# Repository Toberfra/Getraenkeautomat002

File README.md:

# Getraenkeautomat002
Ein Cocktailmixer:

Er Besteht aus mehreren Komponenten:
  - Vielen Peristalik Pumpen.
    - Diese können 3D gedruckt werden. Siehe Hardware/Pumpe/Pumpe3
    - Sie werden von einem Nema 17 Schrittmotor angetrieben.
  - Motor ansteuerung der Schrittmotoren.
    - Sotware für ATmege32
  - Datenbank (MariaDB)
    - Rezepte der Getränke
    - Daten der einzelnen Punmpen
    - Daten der Gläser
  - Sofware zum Bestellen und Ansteuerung der Pumpen

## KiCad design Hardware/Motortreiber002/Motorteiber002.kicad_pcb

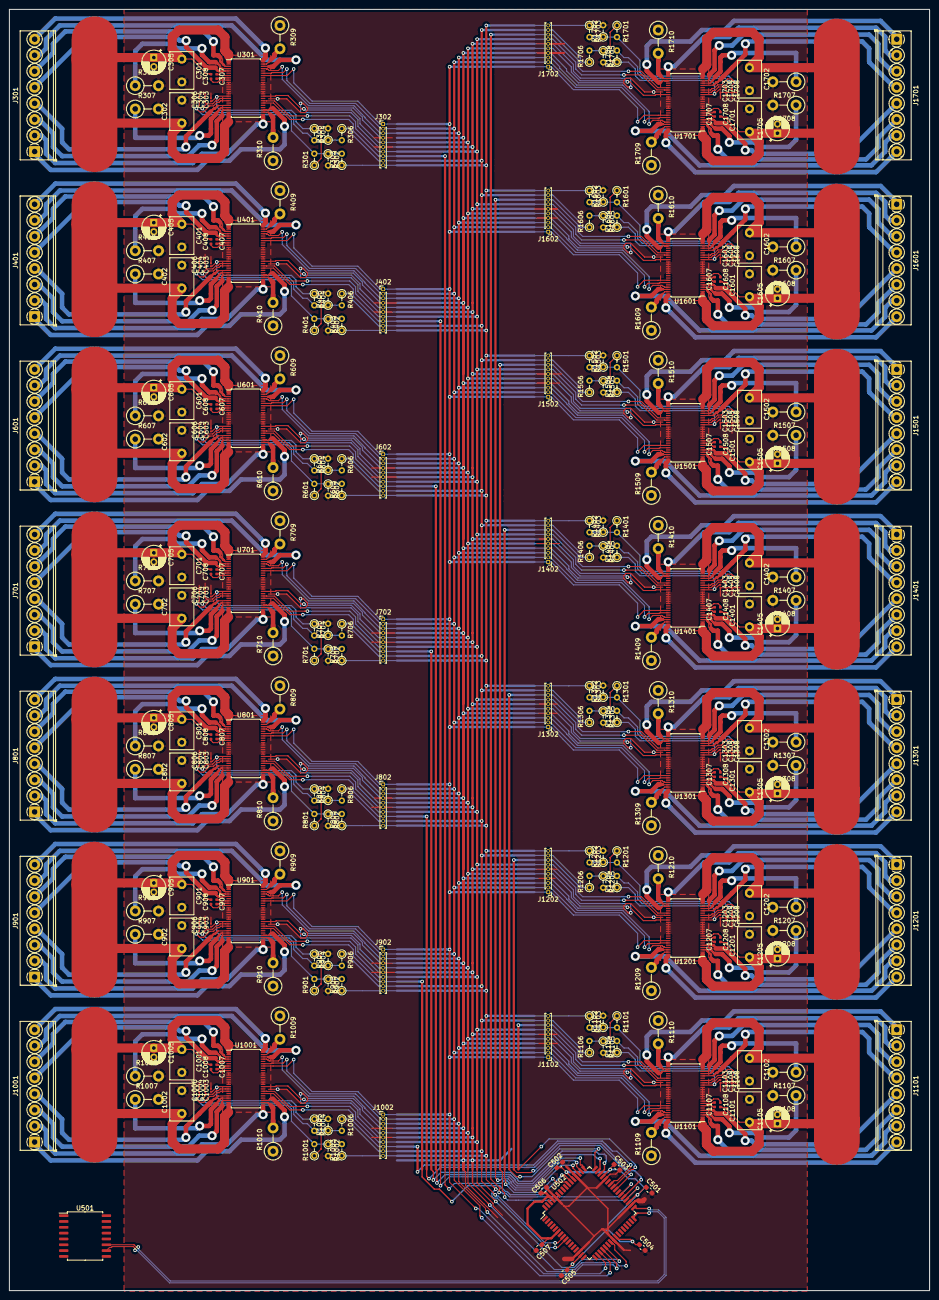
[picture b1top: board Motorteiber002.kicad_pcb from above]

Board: 2 copper layers, 200.7 x 279.4 mm, 303 parts (0 on the bottom side), 292 nets.

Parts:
C301, C302, C401, C402, C601, C602, C701, C702, C801, C802, C901, C902, C1001, C1002, C1101, C1102, C1201, C1202, C1301, C1302, C1401, C1402, C1501, C1502, C1601, C1602, C1701, C1702: 100nF; C_Disc_D8.0mm_W5.0mm_P5.00mm
C303, C403, C603, C703, C803, C903, C1003, C1103, C1203, C1303, C1403, C1503, C1603, C1703: 100nF 6,3V; C_0201_0603Metric
C304, C306, C404, C406, C604, C606, C704, C706, C804, C806, C904, C906, C1004, C1006, C1104, C1106, C1204, C1206, C1304, C1306, C1404, C1406, C1504, C1506, C1604, C1606, C1704, C1706: 1nF 25V; C_0201_0603Metric
C305, C405, C605, C705, C805, C905, C1005, C1105, C1205, C1305, C1405, C1505, C1605, C1705: 33uF 35V; CP_Radial_D5.0mm_P2.00mm
C307, C407, C607, C707, C807, C907, C1007, C1107, C1207, C1307, C1407, C1507, C1607, C1707: 10nF 50V; C_0402_1005Metric
C308, C408, C608, C708, C808, C908, C1008, C1108, C1208, C1308, C1408, C1508, C1608, C1708: 100nF 16V; C_0402_1005Metric
C501, C502, C503, C504, C505, C506, C507: 100nF; C_0603_1608Metric_Pad1.05x0.95mm_HandSolder
J301, J401, J601, J701, J801, J901, J1001, J1101, J1201, J1301, J1401, J1501, J1601, J1701: Screw_Terminal_01x08; TerminalBlock_Phoenix_PT-1,5-8-3.5-H_1x08_P3.50mm_Horizontal
J302, J402, J602, J702, J802, J902, J1002, J1102, J1202, J1302, J1402, J1502, J1602, J1702: Conn_01x10_Male; PinHeader_1x10_P1.00mm_Vertical
R301, R302, R304, R305, R401, R402, R404, R405, R601, R602, R604, R605, R701, R702, R704, R705, R801, R802, R804, R805, R901, R902, R904, R905, R1001, R1002, R1004, R1005, R1101, R1102, R1104, R1105, R1201, R1202, R1204, R1205, R1301, R1302, R1304, R1305, R1401, R1402, R1404, R1405, R1501, R1502, R1504, R1505, R1601, R1602, R1604, R1605, R1701, R1702, R1704, R1705: R; R_Axial_DIN0204_L3.6mm_D1.6mm_P2.54mm_Vertical
R303, R306, R403, R406, R603, R606, R703, R706, R803, R806, R903, R906, R1003, R1006, R1103, R1106, R1203, R1206, R1303, R1306, R1403, R1406, R1503, R1506, R1603, R1606, R1703, R1706: 1; R_Axial_DIN0204_L3.6mm_D1.6mm_P2.54mm_Vertical
R307, R308, R309, R310, R407, R408, R409, R410, R607, R608, R609, R610, R707, R708, R709, R710, R807, R808, R809, R810, R907, R908, R909, R910, R1007, R1008, R1009, R1010, R1107, R1108, R1109, R1110, R1207, R1208, R1209, R1210, R1307, R1308, R1309, R1310, R1407, R1408, R1409, R1410, R1507, R1508, R1509, R1510, R1607, R1608, R1609, R1610, R1707, R1708, R1709, R1710: 0R5; R_Axial_DIN0411_L9.9mm_D3.6mm_P5.08mm_Vertical
U301, U401, U601, U701, U801, U901, U1001, U1101, U1201, U1301, U1401, U1501, U1601, U1701: DRV8823; TSSOP-48_6.1x12.5mm_P0.5mm
U501: ADUM3160; SOIC-16W_7.5x10.3mm_P1.27mm
U502: ATxmega128C3-AU; TQFP-64_14x14mm_P0.8mm

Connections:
+5V: C501.1, C502.1, C503.1, C504.1, C505.1, U502.15, U502.25, U502.35, U502.45, U502.53
+5VA: C506.1, C507.1, U502.6, U502.61
/Controller/D+: U501.10, U502.33
/Controller/D-: U501.11, U502.32
/Motortreiber0/MA1: J701.5, U701.5
/Motortreiber0/MA2: J701.6, U701.3
/Motortreiber0/MAR: R708.1, U701.4
/Motortreiber0/MB1: J701.7, U701.46
/Motortreiber0/MB2: J701.8, U701.48
/Motortreiber0/MBR: R709.2, U701.47
/Motortreiber0/MC1: J701.1, U701.27
/Motortreiber0/MC2: J701.2, U701.25
/Motortreiber0/MCR: R710.2, U701.26
/Motortreiber0/MD1: J701.3, U701.22
/Motortreiber0/MD2: J701.4, U701.20
/Motortreiber0/MDR: R707.1, U701.21
/Motortreiber1/MA1: J601.5, U601.5
/Motortreiber1/MA2: J601.6, U601.3
/Motortreiber1/MAR: R608.1, U601.4
/Motortreiber1/MB1: J601.7, U601.46
/Motortreiber1/MB2: J601.8, U601.48
/Motortreiber1/MBR: R609.2, U601.47
/Motortreiber1/MC1: J601.1, U601.27
/Motortreiber1/MC2: J601.2, U601.25
/Motortreiber1/MCR: R610.2, U601.26
/Motortreiber1/MD1: J601.3, U601.22
/Motortreiber1/MD2: J601.4, U601.20
/Motortreiber1/MDR: R607.1, U601.21
/Motortreiber2/MA1: J1301.5, U1301.5
/Motortreiber2/MA2: J1301.6, U1301.3
/Motortreiber2/MAR: R1308.1, U1301.4
/Motortreiber2/MB1: J1301.7, U1301.46
/Motortreiber2/MB2: J1301.8, U1301.48
/Motortreiber2/MBR: R1309.2, U1301.47
/Motortreiber2/MC1: J1301.1, U1301.27
/Motortreiber2/MC2: J1301.2, U1301.25
/Motortreiber2/MCR: R1310.2, U1301.26
/Motortreiber2/MD1: J1301.3, U1301.22
/Motortreiber2/MD2: J1301.4, U1301.20
/Motortreiber2/MDR: R1307.1, U1301.21
/Motortreiber3/MA1: J401.5, U401.5
/Motortreiber3/MA2: J401.6, U401.3
/Motortreiber3/MAR: R408.1, U401.4
/Motortreiber3/MB1: J401.7, U401.46
/Motortreiber3/MB2: J401.8, U401.48
/Motortreiber3/MBR: R409.2, U401.47
/Motortreiber3/MC1: J401.1, U401.27
/Motortreiber3/MC2: J401.2, U401.25
/Motortreiber3/MCR: R410.2, U401.26
/Motortreiber3/MD1: J401.3, U401.22
/Motortreiber3/MD2: J401.4, U401.20
/Motortreiber3/MDR: R407.1, U401.21
/Motortreiber4/MA1: J1601.5, U1601.5
/Motortreiber4/MA2: J1601.6, U1601.3
/Motortreiber4/MAR: R1608.1, U1601.4
/Motortreiber4/MB1: J1601.7, U1601.46
/Motortreiber4/MB2: J1601.8, U1601.48
/Motortreiber4/MBR: R1609.2, U1601.47
/Motortreiber4/MC1: J1601.1, U1601.27
/Motortreiber4/MC2: J1601.2, U1601.25
/Motortreiber4/MCR: R1610.2, U1601.26
/Motortreiber4/MD1: J1601.3, U1601.22
/Motortreiber4/MD2: J1601.4, U1601.20
/Motortreiber4/MDR: R1607.1, U1601.21
/Motortreiber5/MA1: J301.5, U301.5
/Motortreiber5/MA2: J301.6, U301.3
/Motortreiber5/MAR: R308.1, U301.4
/Motortreiber5/MB1: J301.7, U301.46
/Motortreiber5/MB2: J301.8, U301.48
/Motortreiber5/MBR: R309.2, U301.47
/Motortreiber5/MC1: J301.1, U301.27
/Motortreiber5/MC2: J301.2, U301.25
/Motortreiber5/MCR: R310.2, U301.26
/Motortreiber5/MD1: J301.3, U301.22
/Motortreiber5/MD2: J301.4, U301.20
/Motortreiber5/MDR: R307.1, U301.21
/Motortreiber6/MA1: J901.5, U901.5
/Motortreiber6/MA2: J901.6, U901.3
/Motortreiber6/MAR: R908.1, U901.4
/Motortreiber6/MB1: J901.7, U901.46
/Motortreiber6/MB2: J901.8, U901.48
/Motortreiber6/MBR: R909.2, U901.47
/Motortreiber6/MC1: J901.1, U901.27
/Motortreiber6/MC2: J901.2, U901.25
/Motortreiber6/MCR: R910.2, U901.26
/Motortreiber6/MD1: J901.3, U901.22
/Motortreiber6/MD2: J901.4, U901.20
/Motortreiber6/MDR: R907.1, U901.21
/Motortreiber7/MA1: J1401.5, U1401.5
/Motortreiber7/MA2: J1401.6, U1401.3
/Motortreiber7/MAR: R1408.1, U1401.4
/Motortreiber7/MB1: J1401.7, U1401.46
/Motortreiber7/MB2: J1401.8, U1401.48
/Motortreiber7/MBR: R1409.2, U1401.47
/Motortreiber7/MC1: J1401.1, U1401.27
/Motortreiber7/MC2: J1401.2, U1401.25
/Motortreiber7/MCR: R1410.2, U1401.26
/Motortreiber7/MD1: J1401.3, U1401.22
/Motortreiber7/MD2: J1401.4, U1401.20
/Motortreiber7/MDR: R1407.1, U1401.21
/Motortreiber8/MA1: J1501.5, U1501.5
/Motortreiber8/MA2: J1501.6, U1501.3
/Motortreiber8/MAR: R1508.1, U1501.4
/Motortreiber8/MB1: J1501.7, U1501.46
/Motortreiber8/MB2: J1501.8, U1501.48
/Motortreiber8/MBR: R1509.2, U1501.47
/Motortreiber8/MC1: J1501.1, U1501.27
/Motortreiber8/MC2: J1501.2, U1501.25
/Motortreiber8/MCR: R1510.2, U1501.26
/Motortreiber8/MD1: J1501.3, U1501.22
/Motortreiber8/MD2: J1501.4, U1501.20
/Motortreiber8/MDR: R1507.1, U1501.21
/Motortreiber9/MA1: J801.5, U801.5
/Motortreiber9/MA2: J801.6, U801.3
/Motortreiber9/MAR: R808.1, U801.4
/Motortreiber9/MB1: J801.7, U801.46
/Motortreiber9/MB2: J801.8, U801.48
/Motortreiber9/MBR: R809.2, U801.47
/Motortreiber9/MC1: J801.1, U801.27
/Motortreiber9/MC2: J801.2, U801.25
/Motortreiber9/MCR: R810.2, U801.26
/Motortreiber9/MD1: J801.3, U801.22
/Motortreiber9/MD2: J801.4, U801.20
/Motortreiber9/MDR: R807.1, U801.21
/Motortreiber10/MA1: J1701.5, U1701.5
/Motortreiber10/MA2: J1701.6, U1701.3
/Motortreiber10/MAR: R1708.1, U1701.4
/Motortreiber10/MB1: J1701.7, U1701.46
/Motortreiber10/MB2: J1701.8, U1701.48
/Motortreiber10/MBR: R1709.2, U1701.47
/Motortreiber10/MC1: J1701.1, U1701.27
/Motortreiber10/MC2: J1701.2, U1701.25
/Motortreiber10/MCR: R1710.2, U1701.26
/Motortreiber10/MD1: J1701.3, U1701.22
/Motortreiber10/MD2: J1701.4, U1701.20
/Motortreiber10/MDR: R1707.1, U1701.21
/Motortreiber12/MA1: J1201.5, U1201.5
/Motortreiber12/MA2: J1201.6, U1201.3
/Motortreiber12/MAR: R1208.1, U1201.4
/Motortreiber12/MB1: J1201.7, U1201.46
/Motortreiber12/MB2: J1201.8, U1201.48
/Motortreiber12/MBR: R1209.2, U1201.47
/Motortreiber12/MC1: J1201.1, U1201.27
/Motortreiber12/MC2: J1201.2, U1201.25
/Motortreiber12/MCR: R1210.2, U1201.26
/Motortreiber12/MD1: J1201.3, U1201.22
/Motortreiber12/MD2: J1201.4, U1201.20
/Motortreiber12/MDR: R1207.1, U1201.21
/Motortreiber13/MA1: J1101.5, U1101.5
/Motortreiber13/MA2: J1101.6, U1101.3
/Motortreiber13/MAR: R1108.1, U1101.4
/Motortreiber13/MB1: J1101.7, U1101.46
/Motortreiber13/MB2: J1101.8, U1101.48
/Motortreiber13/MBR: R1109.2, U1101.47
/Motortreiber13/MC1: J1101.1, U1101.27
/Motortreiber13/MC2: J1101.2, U1101.25
/Motortreiber13/MCR: R1110.2, U1101.26
/Motortreiber13/MD1: J1101.3, U1101.22
/Motortreiber13/MD2: J1101.4, U1101.20
/Motortreiber13/MDR: R1107.1, U1101.21
/Motortreiber14/MA1: J1001.5, U1001.5
/Motortreiber14/MA2: J1001.6, U1001.3
/Motortreiber14/MAR: R1008.1, U1001.4
/Motortreiber14/MB1: J1001.7, U1001.46
/Motortreiber14/MB2: J1001.8, U1001.48
/Motortreiber14/MBR: R1009.2, U1001.47
/Motortreiber14/MC1: J1001.1, U1001.27
/Motortreiber14/MC2: J1001.2, U1001.25
/Motortreiber14/MCR: R1010.2, U1001.26
/Motortreiber14/MD1: J1001.3, U1001.22
/Motortreiber14/MD2: J1001.4, U1001.20
/Motortreiber14/MDR: R1007.1, U1001.21
/Steuer0: J302.2, J402.2, J602.2, J702.2, J802.2, J902.2, J1002.2, J1102.2, J1202.2, J1302.2, J1402.2, J1502.2, J1602.2, J1702.2, U301.43, U401.43, U502.19, U601.43, U701.43, U801.43, U901.43, U1001.43, U1101.43, U1201.43, U1301.43, U1401.43, U1501.43, U1601.43, U1701.43
/Steuer1: J302.1, J402.1, J602.1, J702.1, J802.1, J902.1, J1002.1, J1102.1, J1202.1, J1302.1, J1402.1, J1502.1, J1602.1, J1702.1, U301.42, U401.42, U502.18, U601.42, U701.42, U801.42, U901.42, U1001.42, U1101.42, U1201.42, U1301.42, U1401.42, U1501.42, U1601.42, U1701.42
/Steuer2: J302.7, J402.7, J602.7, J702.7, J802.7, J902.7, J1002.7, J1102.7, J1202.7, J1302.7, J1402.7, J1502.7, J1602.7, J1702.7, U301.31, U401.31, U502.21, U601.31, U701.31, U801.31, U901.31, U1001.31, U1101.31, U1201.31, U1301.31, U1401.31, U1501.31, U1601.31, U1701.31
/Steuer3: J302.5, J402.5, J602.5, J702.5, J802.5, J902.5, J1002.5, J1102.5, J1202.5, J1302.5, J1402.5, J1502.5, J1602.5, J1702.5, U301.33, U401.33, U502.23, U601.33, U701.33, U801.33, U901.33, U1001.33, U1101.33, U1201.33, U1301.33, U1401.33, U1501.33, U1601.33, U1701.33
/Steuer4: J302.3, J402.3, J602.3, J702.3, J802.3, J902.3, J1002.3, J1102.3, J1202.3, J1302.3, J1402.3, J1502.3, J1602.3, J1702.3, U301.45, U401.45, U502.20, U601.45, U701.45, U801.45, U901.45, U1001.45, U1101.45, U1201.45, U1301.45, U1401.45, U1501.45, U1601.45, U1701.45
/Steuer5: J302.9, J402.9, J602.9, J702.9, J802.9, J902.9, J1002.9, J1102.9, J1202.9, J1302.9, J1402.9, J1502.9, J1602.9, J1702.9, R306.1, R406.1, R606.1, R706.1, R806.1, R906.1, R1006.1, R1106.1, R1206.1, R1306.1, R1406.1, R1506.1, R1606.1, R1706.1, U502.8
/Steuer6: J302.10, J402.10, J602.10, J702.10, J802.10, J902.10, J1002.10, J1102.10, J1202.10, J1302.10, J1402.10, J1502.10, J1602.10, J1702.10, R303.1, R403.1, R603.1, R703.1, R803.1, R903.1, R1003.1, R1103.1, R1203.1, R1303.1, R1403.1, R1503.1, R1603.1, R1703.1, U502.9
/Strobe0: J702.8, U502.46, U701.30
/Strobe1: J602.8, U502.47, U601.30
/Strobe2: J1302.8, U502.48, U1301.30
/Strobe3: J402.8, U401.30, U502.49
/Strobe4: J1602.8, U502.50, U1601.30
/Strobe5: J302.8, U301.30, U502.51
/Strobe6: J902.8, U502.54, U901.30
/Strobe7: J1402.8, U502.55, U1401.30
/Strobe8: J1502.8, U502.36, U1501.30
/Strobe9: J802.8, U502.37, U801.30
/Strobe10: J1702.8, U502.38, U1701.30
/Strobe12: J1202.8, U502.40, U1201.30
/Strobe13: J1102.8, U502.41, U1101.30
/Strobe14: J1002.8, U502.42, U1001.30
GND: C301.2, C302.2, C303.2, C304.2, C305.2, C306.2, C401.2, C402.2, C403.2, C404.2, C405.2, C406.2, C501.2, C502.2, C503.2, C504.2, C505.2, C506.2, C507.2, C601.2, C602.2, C603.2, C604.2, C605.2, C606.2, C701.2, C702.2, C703.2, C704.2, C705.2, C706.2, C801.2, C802.2, C803.2, C804.2, C805.2, C806.2, C901.2, C902.2, C903.2, C904.2, C905.2, C906.2, C1001.2, C1002.2, C1003.2, C1004.2, C1005.2, C1006.2, C1101.2, C1102.2, C1103.2, C1104.2, C1105.2, C1106.2, C1201.2, C1202.2, C1203.2, C1204.2, C1205.2, C1206.2, C1301.2, C1302.2, C1303.2, C1304.2, C1305.2, C1306.2, C1401.2, C1402.2, C1403.2, C1404.2, C1405.2, C1406.2, C1501.2, C1502.2, C1503.2, C1504.2, C1505.2, C1506.2, C1601.2, C1602.2, C1603.2, C1604.2, C1605.2, C1606.2, C1701.2, C1702.2, C1703.2, C1704.2, C1705.2, C1706.2, J302.4, J302.6, J402.4, J402.6, J602.4, J602.6, J702.4, J702.6, J802.4, J802.6, J902.4, J902.6, J1002.4, J1002.6, J1102.4, J1102.6, J1202.4, J1202.6, J1302.4, J1302.6, J1402.4, J1402.6, J1502.4, J1502.6, J1602.4, J1602.6, J1702.4, J1702.6, R302.2, R305.2, R307.2, R308.2, R309.1, R310.1, R402.2, R405.2, R407.2, R408.2, R409.1, R410.1, R602.2, R605.2, R607.2, R608.2, R609.1, R610.1, R702.2, R705.2, R707.2, R708.2, R709.1, R710.1, R802.2, R805.2, R807.2, R808.2, R809.1, R810.1, R902.2, R905.2, R907.2, R908.2, R909.1, R910.1, R1002.2, R1005.2, R1007.2, R1008.2, R1009.1, R1010.1, R1102.2, R1105.2, R1107.2, R1108.2, R1109.1, R1110.1, R1202.2, R1205.2, R1207.2, R1208.2, R1209.1, R1210.1, R1302.2, R1305.2, R1307.2, R1308.2, R1309.1, R1310.1, R1402.2, R1405.2, R1407.2, R1408.2, R1409.1, R1410.1, R1502.2, R1505.2, R1507.2, R1508.2, R1509.1, R1510.1, R1602.2, R1605.2, R1607.2, R1608.2, R1609.1, R1610.1, R1702.2, R1705.2, R1707.2, R1708.2, R1709.1, R1710.1, U301.10, U301.11, U301.12, U301.13, U301.14, U301.15, U301.34, U301.35, U301.36, U301.37, U301.38, U301.39, U401.10, U401.11, U401.12, U401.13, U401.14, U401.15, U401.34, U401.35, U401.36, U401.37, U401.38, U401.39, U502.14, U502.24, U502.34, U502.44, U502.52, U502.60, U601.10, U601.11, U601.12, U601.13, U601.14, U601.15, U601.34, U601.35, U601.36, U601.37, U601.38, U601.39, U701.10, U701.11, U701.12, U701.13, U701.14, U701.15, U701.34, U701.35, U701.36, U701.37, U701.38, U701.39, U801.10, U801.11, U801.12, U801.13, U801.14, U801.15, U801.34, U801.35, U801.36, U801.37, U801.38, U801.39, U901.10, U901.11, U901.12, U901.13, U901.14, U901.15, U901.34, U901.35, U901.36, U901.37, U901.38, U901.39, U1001.10, U1001.11, U1001.12, U1001.13, U1001.14, U1001.15, U1001.34, U1001.35, U1001.36, U1001.37, U1001.38, U1001.39, U1101.10, U1101.11, U1101.12, U1101.13, U1101.14, U1101.15, U1101.34, U1101.35, U1101.36, U1101.37, U1101.38, U1101.39, U1201.10, U1201.11, U1201.12, U1201.13, U1201.14, U1201.15, U1201.34, U1201.35, U1201.36, U1201.37, U1201.38, U1201.39, U1301.10, U1301.11, U1301.12, U1301.13, U1301.14, U1301.15, U1301.34, U1301.35, U1301.36, U1301.37, U1301.38, U1301.39, U1401.10, U1401.11, U1401.12, U1401.13, U1401.14, U1401.15, U1401.34, U1401.35, U1401.36, U1401.37, U1401.38, U1401.39, U1501.10, U1501.11, U1501.12, U1501.13, U1501.14, U1501.15, U1501.34, U1501.35, U1501.36, U1501.37, U1501.38, U1501.39, U1601.10, U1601.11, U1601.12, U1601.13, U1601.14, U1601.15, U1601.34, U1601.35, U1601.36, U1601.37, U1601.38, U1601.39, U1701.10, U1701.11, U1701.12, U1701.13, U1701.14, U1701.15, U1701.34, U1701.35, U1701.36, U1701.37, U1701.38, U1701.39
unnamed: C301.1, C302.1, C305.1, C308.2, U301.1, U301.2, U301.23, U301.24
unnamed: C303.1, R301.1, R304.1, U301.16
unnamed: C304.1, R304.2, R305.1, R306.2, U301.17
unnamed: C306.1, R301.2, R302.1, R303.2, U301.18
unnamed: C307.1, U301.7
unnamed: C307.2, U301.8
unnamed: C308.1, U301.9
unnamed: C401.1, C402.1, C405.1, C408.2, U401.1, U401.2, U401.23, U401.24
unnamed: C403.1, R401.1, R404.1, U401.16
unnamed: C404.1, R404.2, R405.1, R406.2, U401.17
unnamed: C406.1, R401.2, R402.1, R403.2, U401.18
unnamed: C407.1, U401.7
unnamed: C407.2, U401.8
unnamed: C408.1, U401.9
unnamed: C601.1, C602.1, C605.1, C608.2, U601.1, U601.2, U601.23, U601.24
unnamed: C603.1, R601.1, R604.1, U601.16
unnamed: C604.1, R604.2, R605.1, R606.2, U601.17
unnamed: C606.1, R601.2, R602.1, R603.2, U601.18
unnamed: C607.1, U601.7
unnamed: C607.2, U601.8
unnamed: C608.1, U601.9
unnamed: C701.1, C702.1, C705.1, C708.2, U701.1, U701.2, U701.23, U701.24
unnamed: C703.1, R701.1, R704.1, U701.16
unnamed: C704.1, R704.2, R705.1, R706.2, U701.17
unnamed: C706.1, R701.2, R702.1, R703.2, U701.18
unnamed: C707.1, U701.7
unnamed: C707.2, U701.8
unnamed: C708.1, U701.9
unnamed: C801.1, C802.1, C805.1, C808.2, U801.1, U801.2, U801.23, U801.24
unnamed: C803.1, R801.1, R804.1, U801.16
unnamed: C804.1, R804.2, R805.1, R806.2, U801.17
unnamed: C806.1, R801.2, R802.1, R803.2, U801.18
unnamed: C807.1, U801.7
unnamed: C807.2, U801.8
unnamed: C808.1, U801.9
unnamed: C901.1, C902.1, C905.1, C908.2, U901.1, U901.2, U901.23, U901.24
unnamed: C903.1, R901.1, R904.1, U901.16
unnamed: C904.1, R904.2, R905.1, R906.2, U901.17
unnamed: C906.1, R901.2, R902.1, R903.2, U901.18
unnamed: C907.1, U901.7
unnamed: C907.2, U901.8
unnamed: C908.1, U901.9
unnamed: C1001.1, C1002.1, C1005.1, C1008.2, U1001.1, U1001.2, U1001.23, U1001.24
unnamed: C1003.1, R1001.1, R1004.1, U1001.16
unnamed: C1004.1, R1004.2, R1005.1, R1006.2, U1001.17
unnamed: C1006.1, R1001.2, R1002.1, R1003.2, U1001.18
unnamed: C1007.1, U1001.7
unnamed: C1007.2, U1001.8
unnamed: C1008.1, U1001.9
unnamed: C1101.1, C1102.1, C1105.1, C1108.2, U1101.1, U1101.2, U1101.23, U1101.24
unnamed: C1103.1, R1101.1, R1104.1, U1101.16
unnamed: C1104.1, R1104.2, R1105.1, R1106.2, U1101.17
unnamed: C1106.1, R1101.2, R1102.1, R1103.2, U1101.18
unnamed: C1107.1, U1101.7
unnamed: C1107.2, U1101.8
unnamed: C1108.1, U1101.9
unnamed: C1201.1, C1202.1, C1205.1, C1208.2, U1201.1, U1201.2, U1201.23, U1201.24
unnamed: C1203.1, R1201.1, R1204.1, U1201.16
unnamed: C1204.1, R1204.2, R1205.1, R1206.2, U1201.17
unnamed: C1206.1, R1201.2, R1202.1, R1203.2, U1201.18
unnamed: C1207.1, U1201.7
unnamed: C1207.2, U1201.8
unnamed: C1208.1, U1201.9
unnamed: C1301.1, C1302.1, C1305.1, C1308.2, U1301.1, U1301.2, U1301.23, U1301.24
unnamed: C1303.1, R1301.1, R1304.1, U1301.16
unnamed: C1304.1, R1304.2, R1305.1, R1306.2, U1301.17
unnamed: C1306.1, R1301.2, R1302.1, R1303.2, U1301.18
unnamed: C1307.1, U1301.7
unnamed: C1307.2, U1301.8
unnamed: C1308.1, U1301.9
unnamed: C1401.1, C1402.1, C1405.1, C1408.2, U1401.1, U1401.2, U1401.23, U1401.24
unnamed: C1403.1, R1401.1, R1404.1, U1401.16
unnamed: C1404.1, R1404.2, R1405.1, R1406.2, U1401.17
unnamed: C1406.1, R1401.2, R1402.1, R1403.2, U1401.18
unnamed: C1407.1, U1401.7
unnamed: C1407.2, U1401.8
unnamed: C1408.1, U1401.9
unnamed: C1501.1, C1502.1, C1505.1, C1508.2, U1501.1, U1501.2, U1501.23, U1501.24
unnamed: C1503.1, R1501.1, R1504.1, U1501.16
unnamed: C1504.1, R1504.2, R1505.1, R1506.2, U1501.17
unnamed: C1506.1, R1501.2, R1502.1, R1503.2, U1501.18
unnamed: C1507.1, U1501.7
unnamed: C1507.2, U1501.8
unnamed: C1508.1, U1501.9
unnamed: C1601.1, C1602.1, C1605.1, C1608.2, U1601.1, U1601.2, U1601.23, U1601.24
unnamed: C1603.1, R1601.1, R1604.1, U1601.16
unnamed: C1604.1, R1604.2, R1605.1, R1606.2, U1601.17
unnamed: C1606.1, R1601.2, R1602.1, R1603.2, U1601.18
unnamed: C1607.1, U1601.7
unnamed: C1607.2, U1601.8
unnamed: C1608.1, U1601.9
unnamed: C1701.1, C1702.1, C1705.1, C1708.2, U1701.1, U1701.2, U1701.23, U1701.24
unnamed: C1703.1, R1701.1, R1704.1, U1701.16
unnamed: C1704.1, R1704.2, R1705.1, R1706.2, U1701.17
unnamed: C1706.1, R1701.2, R1702.1, R1703.2, U1701.18
unnamed: C1707.1, U1701.7
unnamed: C1707.2, U1701.8
unnamed: C1708.1, U1701.9

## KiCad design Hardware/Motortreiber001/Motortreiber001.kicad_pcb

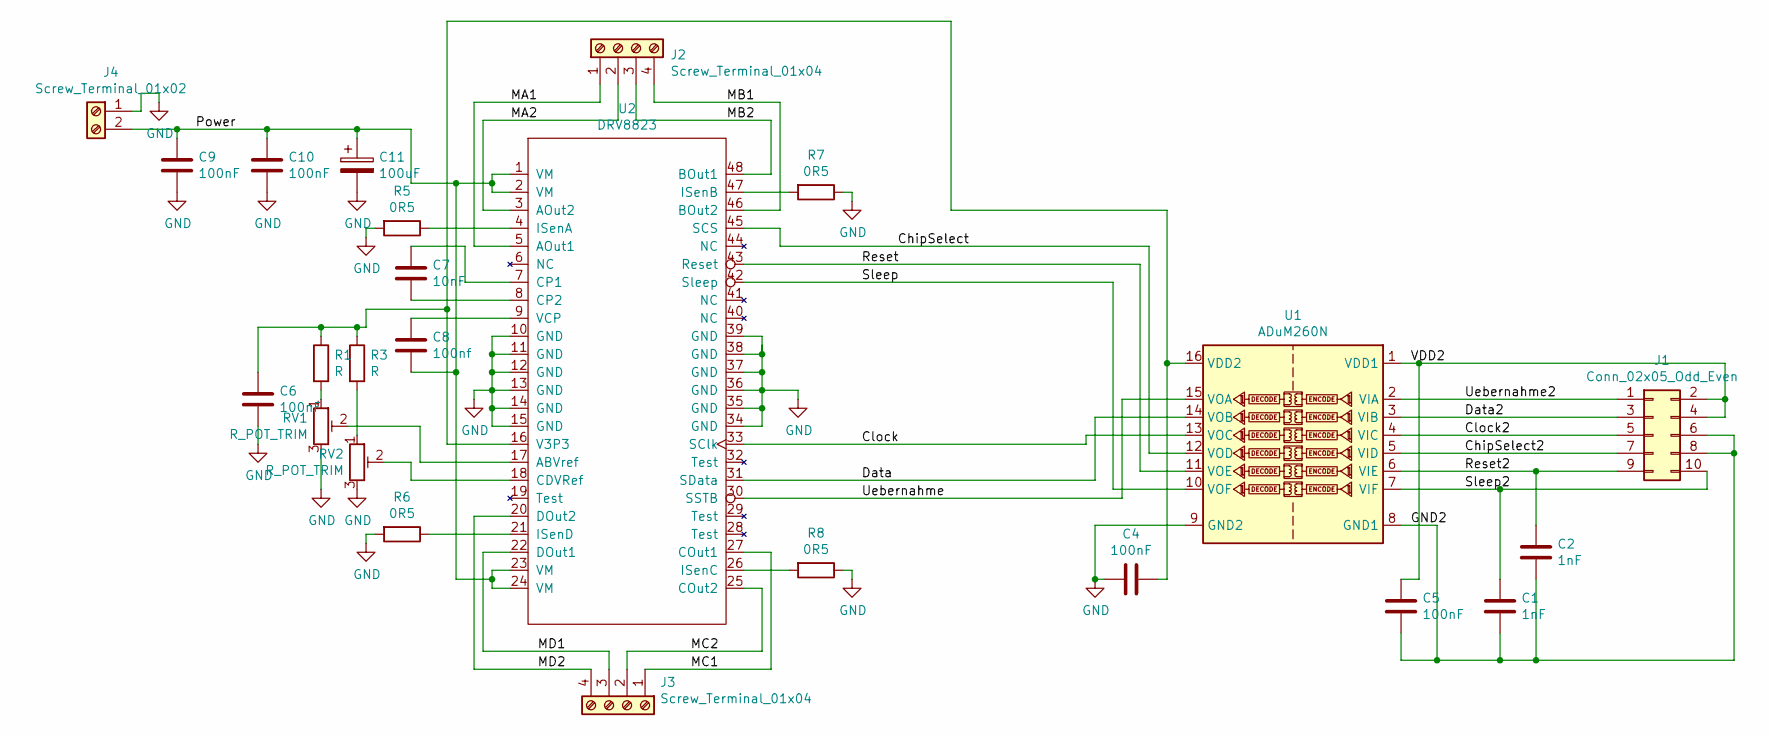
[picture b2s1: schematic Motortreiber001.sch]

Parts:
C1, C2: 1nF; C_0805_2012Metric
C4, C6: 100nF; C_0805_2012Metric_Pad1.15x1.40mm_HandSolder
C5: 100nF; C_Disc_D7.5mm_W2.5mm_P5.00mm
C7: 10nF; C_0805_2012Metric
C8: 100nf; C_0805_2012Metric_Pad1.15x1.40mm_HandSolder
C9, C10: 100nF; C_Disc_D8.0mm_W5.0mm_P5.00mm
C11: 100uF; CP_Radial_D8.0mm_P3.50mm
J1: Conn_02x05_Odd_Even; PinSocket_2x05_P2.54mm_Vertical
J2, J3: Screw_Terminal_01x04; PhoenixContact_MCV_1,5_4-G-5.08_1x04_P5.08mm_Vertical
J4: Screw_Terminal_01x02; PhoenixContact_MCV_1,5_2-G-5.08_1x02_P5.08mm_Vertical
R1, R3: R; R_0805_2012Metric_Pad1.15x1.40mm_HandSolder
R5, R6, R7, R8: 0R5; R_Axial_DIN0411_L9.9mm_D3.6mm_P5.08mm_Vertical
RV1, RV2: R_POT_TRIM; Potentiometer_Vishay_43_Horizontal
U1: ADuM260N; SOIC-16W_7.5x12.8mm_P1.27mm
U2: DRV8823; TSSOP-48_6.1x12.5mm_P0.5mm

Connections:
/ChipSelect: U1.12 (VOD), U2.45 (SCS)
/ChipSelect2: J1.7, U1.5 (VID)
/Clock: U1.13 (VOC), U2.33 (SClk)
/Clock2: J1.5, U1.4 (VIC)
/Data: U1.14 (VOB), U2.31 (SData)
/Data2: J1.3, U1.3 (VIB)
/GND2: C1.2, C2.2, C5.1, J1.6, J1.8, U1.8 (GND1)
/MA1: J2.1, U2.5 (AOut1)
/MA2: J2.2, U2.3 (AOut2)
/MB1: J2.4, U2.46 (BOut2)
/MB2: J2.3, U2.48 (BOut1)
/MC1: J3.1, U2.27 (COut1)
/MC2: J3.2, U2.25 (COut2)
/MD1: J3.3, U2.22 (DOut1)
/MD2: J3.4, U2.20 (DOut2)
/Power: C8.2, C9.1, C10.1, C11.1, J4.2, U2.1 (VM), U2.2 (VM), U2.23 (VM), U2.24 (VM)
/Reset: U1.11 (VOE), U2.43 (Reset)
/Reset2: C2.1, J1.9, U1.6 (VIE)
/Sleep: U1.10 (VOF), U2.42 (Sleep)
/Sleep2: C1.1, J1.10, U1.7 (VIF)
/Uebernahme: U1.15 (VOA), U2.30 (SSTB)
/Uebernahme2: J1.1, U1.2 (VIA)
/VDD2: C5.2, J1.2, J1.4, U1.1 (VDD1)
GND: C4.2, C6.2, C9.2, C10.2, C11.2, J4.1, R5.2, R6.2, R7.1, R8.1, RV1.3, RV2.3, U1.9 (GND2), U2.10 (GND), U2.11 (GND), U2.12 (GND), U2.13 (GND), U2.14 (GND), U2.15 (GND), U2.34 (GND), U2.35 (GND), U2.36 (GND), U2.37 (GND), U2.38 (GND), U2.39 (GND)
unnamed: C4.1, C6.1, R1.1, R3.1, U1.16 (VDD2), U2.16 (V3P3)
unnamed: C7.1, U2.7 (CP1)
unnamed: C7.2, U2.8 (CP2)
unnamed: C8.1, U2.9 (VCP)
unnamed: R1.2, RV1.1
unnamed: R3.2, RV2.1
unnamed: R5.1, U2.4 (ISenA)
unnamed: R6.1, U2.21 (ISenD)
unnamed: R7.2, U2.47 (ISenB)
unnamed: R8.2, U2.26 (ISenC)
unnamed: RV1.2, U2.17 (ABVref)
unnamed: RV2.2, U2.18 (CDVRef)

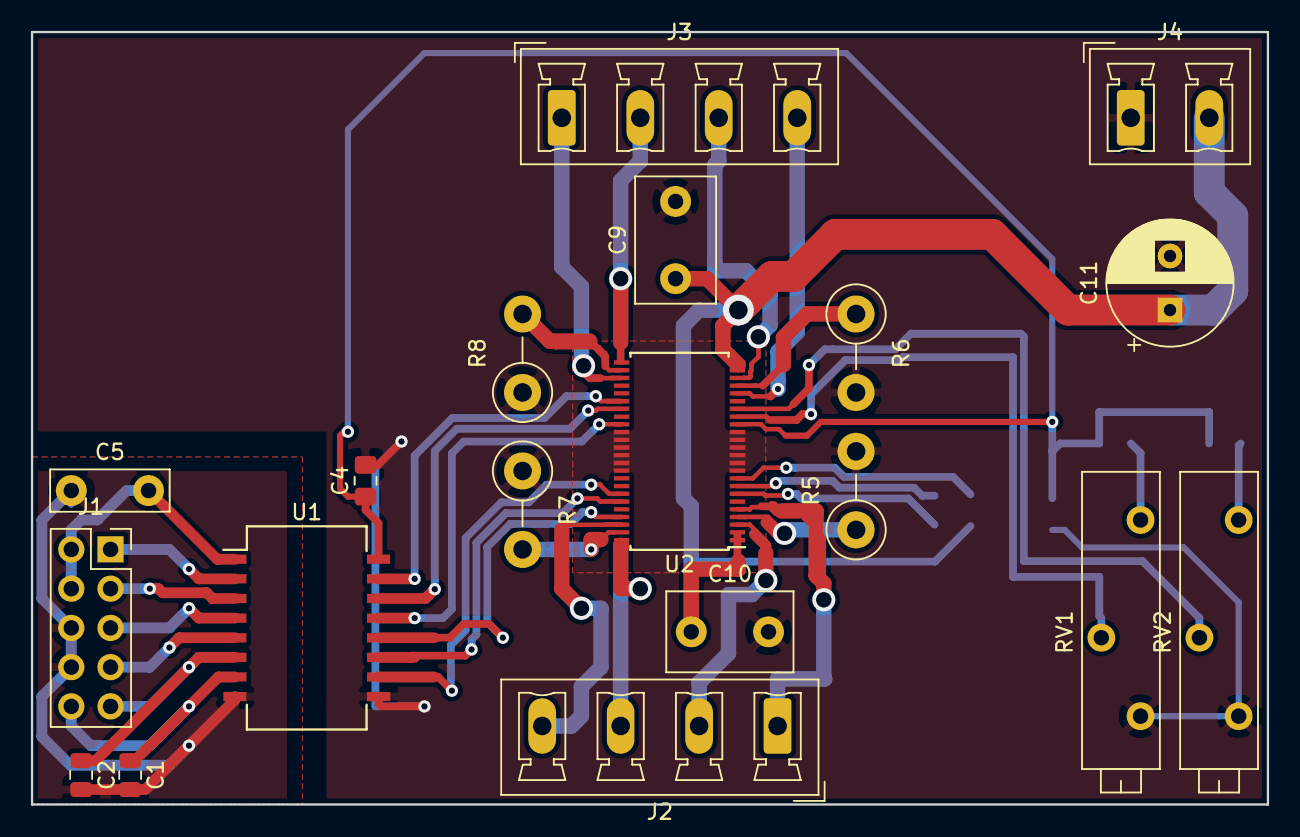
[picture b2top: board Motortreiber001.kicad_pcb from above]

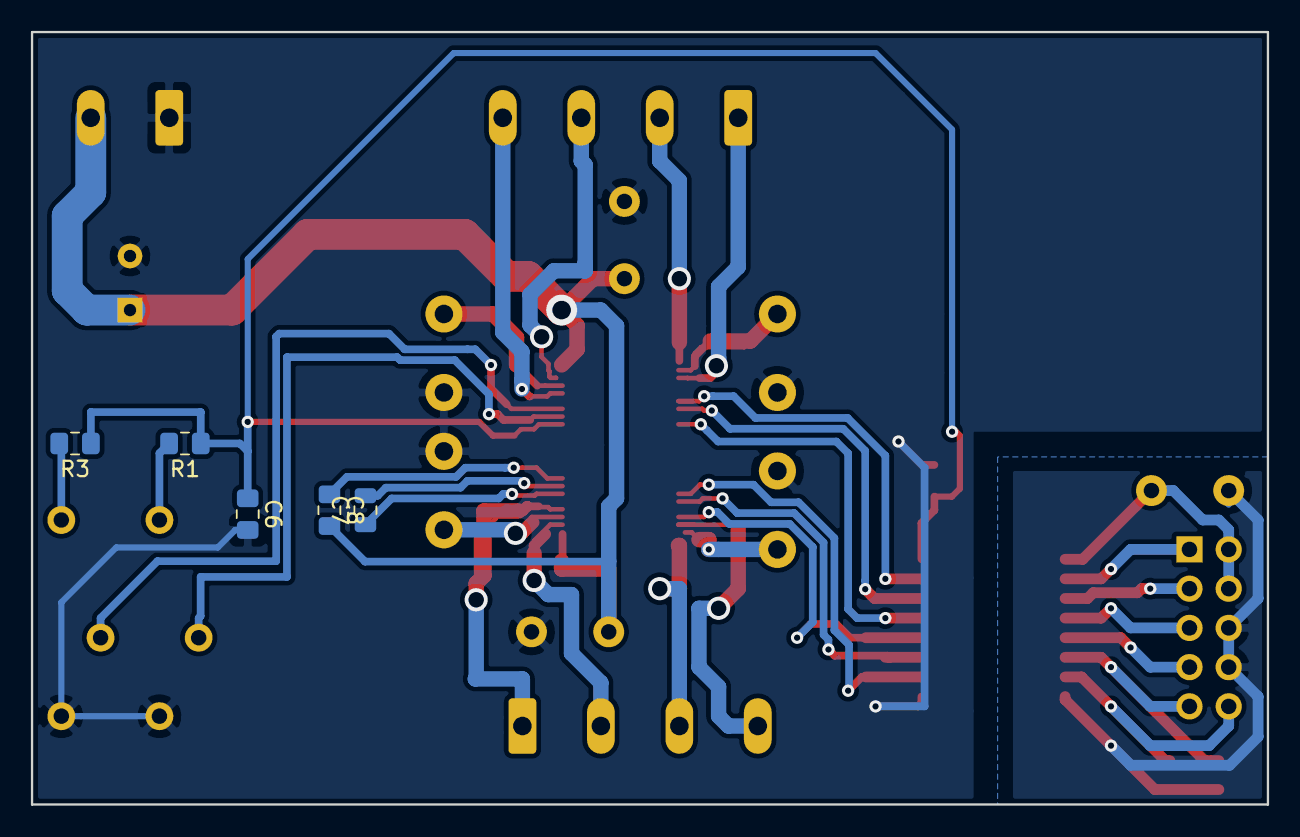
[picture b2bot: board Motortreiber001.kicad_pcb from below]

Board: 2 copper layers, 80.0 x 50.0 mm, 24 parts (5 on the bottom side), 36 nets.

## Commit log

2019-04-08 unnoetige Dateien geloescht.
2019-04-08 Schriftfeld ausgefuellt
2019-04-08 90° gedreht
2019-04-09 Create LICENSE
2019-04-09 von ADum auf RS422 umbauen
2019-04-09 Datenblatt Motortreiber hinzu
2019-04-09 .gitignore mit *.bak hinzu
2019-04-12 Motortreiber Platine mit 4 DRV8823
2019-04-13 Mega64 hinzu
2019-04-19 Umbau auf ATXMega128 Start
2019-04-19 16 Motortreiber 1 ATXMega 128 mit USB USB Anschluss noch nicht fertig
2019-04-21 Annotation auf Seiten bezogen
2019-04-21 platzierung angefangen
2019-04-21 Erster Motoreiber angefangen routen
2019-04-22 Kondensatoren auf SMD geaendert
2019-04-22 weiteres routing
2019-04-25 16 Motortreiber
2019-04-25 Aenderungen
2019-04-27 Layout 16 Motortreiber grob fertig
2019-04-27 erster Treiber am Bus angeschlossen
2019-04-27 erster Treiber neu am Bus angebunden
2019-04-27 Mittlerer Bus verschoben Fehler in Steuer2
2019-04-28 weitere Motortreiber am Bus angebunden
2019-04-29 Ausgabe gedreht
2019-12-25 Test
2020-01-17 falsche Daten
2020-08-01 AtMega 32 hinzu
2020-08-01 Datenblaetter hinzu
2020-08-01 Motortreiber letzte Aenderungen
2020-08-01 Schrittmotor Ansteuerung c++ hinzu
2020-08-02 Motor dreht mit gewaehlter drehzahl
2020-08-03 Beschreibung geaendert
2020-08-05 3D Pumpe hinzu
2020-08-07 Bescreibungen hinzu
2020-08-07 Beide drehrichtungen
2020-08-08 Befehl Power und ups sind OK
2020-08-08 Angefangen mit Umdrehungen in vorgegebener Zeit
2020-08-08 Befehl umdr jetzt mit Funktion
2020-08-10 Kommunikation Arduino und Python klappt mit 9600
2024-06-27 User auf remote geaendert
